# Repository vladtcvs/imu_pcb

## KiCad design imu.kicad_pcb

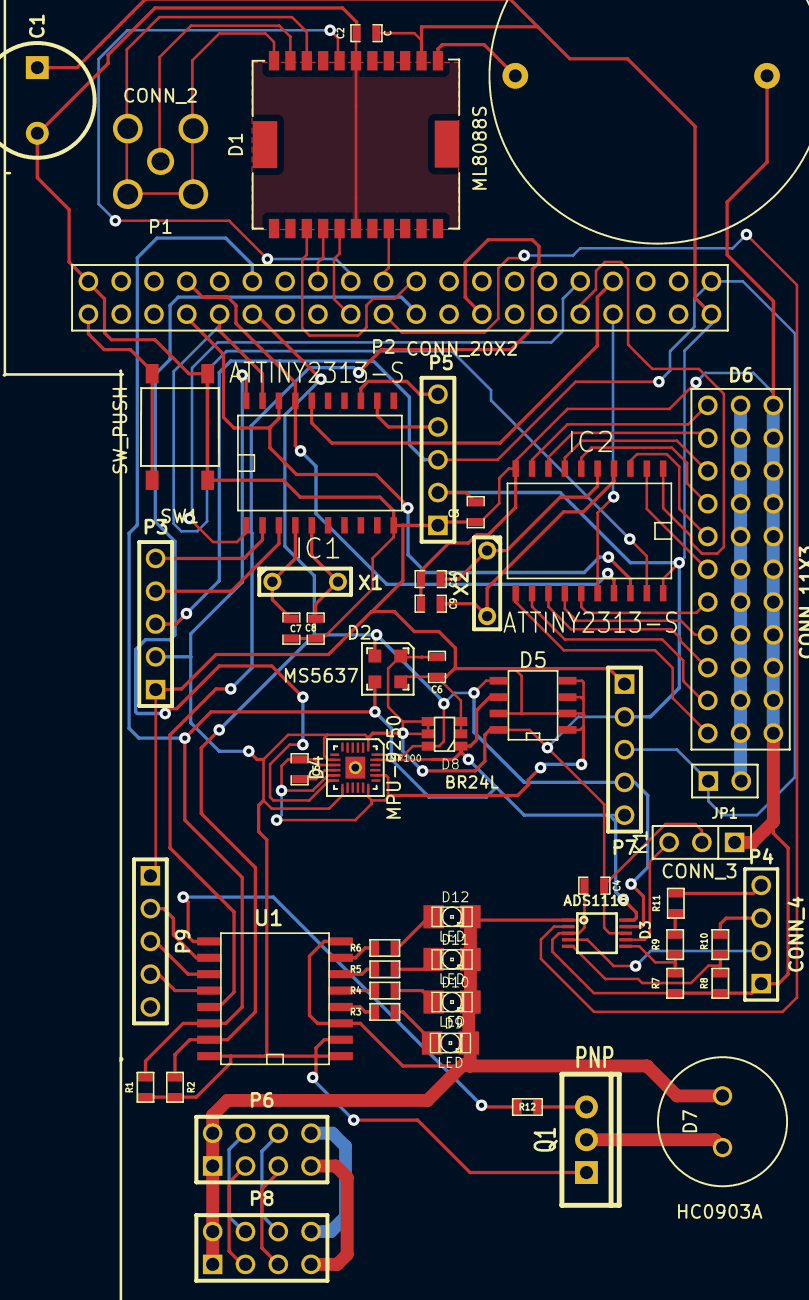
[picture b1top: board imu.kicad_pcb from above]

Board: 2 copper layers, 53 parts (0 on the bottom side), 72 nets.

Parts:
BT1: BATTERY; battery
C1: CP1; C2V8
C2, C3, C4, C5, C6, C7, C8, C9, C10: C; SM0603_Capa
D1: ML8088S; ml8088sE
D2: MS5637; qfn-4
D3: ADS1115; MSOP10-0.5
D4: MPU-9250; qfn24
D5: BR24L; SO8E
D6: CONN_11X3; pin_array_11x3
D7: HC0903A
D8: TMP100; SOT23_6
D9, D10, D11, D12: LED; LED-1206
IC1, IC2: ATTINY2313-S; SO20L
JP1: JUMPER; PIN_ARRAY_2X1
K1: CONN_3; PIN_ARRAY_3X1
P1: CONN_2; sma
P2: CONN_20X2; conn_20x2
P3, P5, P7: CONN_5; PIN_ARRAY_5x1
P4: CONN_4; PIN_ARRAY_4x1
P6, P8: CONN_4X2; pin_array_4x2
P9: CONN_4; PIN_ARRAY_5x1
Q1: PNP; TO220_VERT
R1, R2, R3, R4, R5, R6, R7, R8, R9, R10, R11, R12: R; SM0603
SW1: SW_PUSH; button4
U1: PCF8574; SO16L
X1, X2: CRYSTAL; C2

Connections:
/3.3V: C1.1, C2.1, C3.1, C4.2, C6.1, D1.13, D2.1, D3.8, D4.1, D4.8, D4.13, D5.8, D8.4, D8.5, IC1.20, IC2.20, K1.2, P2.2, P3.2, P5.2, P7.2, Q1.1, R1.1, R2.1, U1.1, U1.2, U1.16
/5V: JP1.1, P2.1, P3.3, P5.3, P7.3
/ADC_RDY: D3.2, P2.22
/CLK: IC1.19, IC2.19, P2.32
/CS0: IC1.16, P2.7
/CS1: IC2.16, P2.8
/GND: BT1.2, C1.2, C2.2, C3.2, C4.1, C5.2, C6.2, C7.2, C8.2, C9.1, C10.1, D1.6, D1.17, D2.4, D3.1, D3.3, D4.9, D4.11, D4.18, D4.20, D5.1, D5.2, D5.3, D5.4, D5.7, D6.3, D6.6, D6.9, D6.12, D6.15, D6.18, D6.21, D6.24, D6.27, D6.30, D6.33, D7.-, D8.2, D8.3, D9.2, D10.2, D11.2, D12.2, IC1.10, IC2.10, K1.1, P2.39, P3.1, P4.1, P5.1, P6.1, P6.2, P7.1, P8.1, P8.2, P9.1, R7.1, R8.1, SW1.1, U1.3, U1.8
/GPIO_INT: P2.16, U1.13
/GPS_PPS: D1.3, P2.19
/GPS_RST: D1.18, P2.23
/GPS_STATUS: D1.8, P2.21
/IMU_INT: D4.12, P2.20
/MISO: IC1.18, IC2.18, P2.34
/MOSI: IC1.17, IC2.17, P2.33
/RST0: IC1.1, P2.9
/RST1: IC2.1, P2.10
/SCL: D2.3, D3.10, D4.23, D5.6, D8.1, P2.29, P7.5, R1.2, U1.14
/SDA: D2.2, D3.9, D4.24, D5.5, D8.6, P2.30, P7.4, R2.2, U1.15
unnamed: IC1.3, P3.4
unnamed: D3.5, R8.2, R10.1
unnamed: C5.1, D4.10
unnamed: D1.4, P2.25
unnamed: D1.21, P1.2
unnamed: BT1.1, D1.12
unnamed: D3.7, K1.3
unnamed: P2.40, SW1.2
unnamed: D1.5, P2.24
unnamed: D6.28, IC2.12
unnamed: D6.22, IC2.14
unnamed: D6.16, IC2.2
unnamed: D6.13, IC2.3
unnamed: D6.10, IC2.6
unnamed: D6.4, IC2.8
unnamed: D6.31, IC2.11
unnamed: P4.4, R11.2
unnamed: P4.3, R10.2
unnamed: D3.4, P4.2
unnamed: D6.2, D6.5, D6.8, D6.11, D6.14, D6.17, D6.20, D6.23, D6.26, D6.29, D6.32, JP1.2
unnamed: D1.20, D1.22, P1.1
unnamed: D6.7, IC2.7
unnamed: D6.1, IC2.9
unnamed: D6.19, IC2.15
unnamed: D3.6, R7.2, R9.1
unnamed: R9.2, R11.1
unnamed: P6.6, P8.6
unnamed: P6.8, P8.8
unnamed: Q1.2, R12.1
unnamed: P9.3, U1.11
unnamed: P9.4, U1.12
unnamed: D7.+, Q1.3
unnamed: P6.5, P8.5
unnamed: P6.3, P8.3
unnamed: P6.7, P8.7
unnamed: P6.4, P8.4
unnamed: R3.1, U1.4
unnamed: R4.1, U1.5
unnamed: R5.1, U1.6
unnamed: R6.1, U1.7
unnamed: D12.1, R6.2
unnamed: D11.1, R5.2
unnamed: D10.1, R4.2
unnamed: D9.1, R3.2
unnamed: R12.2, U1.9
unnamed: P9.2, U1.10
unnamed: IC1.2, P3.5
unnamed: D6.25, IC2.13
unnamed: IC1.13, P5.5
unnamed: IC1.12, P5.4
unnamed: C8.1, IC1.4, X1.1
unnamed: C7.1, IC1.5, X1.2
unnamed: C10.2, IC2.5, X2.1
unnamed: C9.2, IC2.4, X2.2

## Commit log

2015-02-09 initial revision
2015-02-20 silk back
2015-04-14 pcb and elements
2015-07-02 restore
2015-07-04 add license
2015-07-04 add cmp and net
